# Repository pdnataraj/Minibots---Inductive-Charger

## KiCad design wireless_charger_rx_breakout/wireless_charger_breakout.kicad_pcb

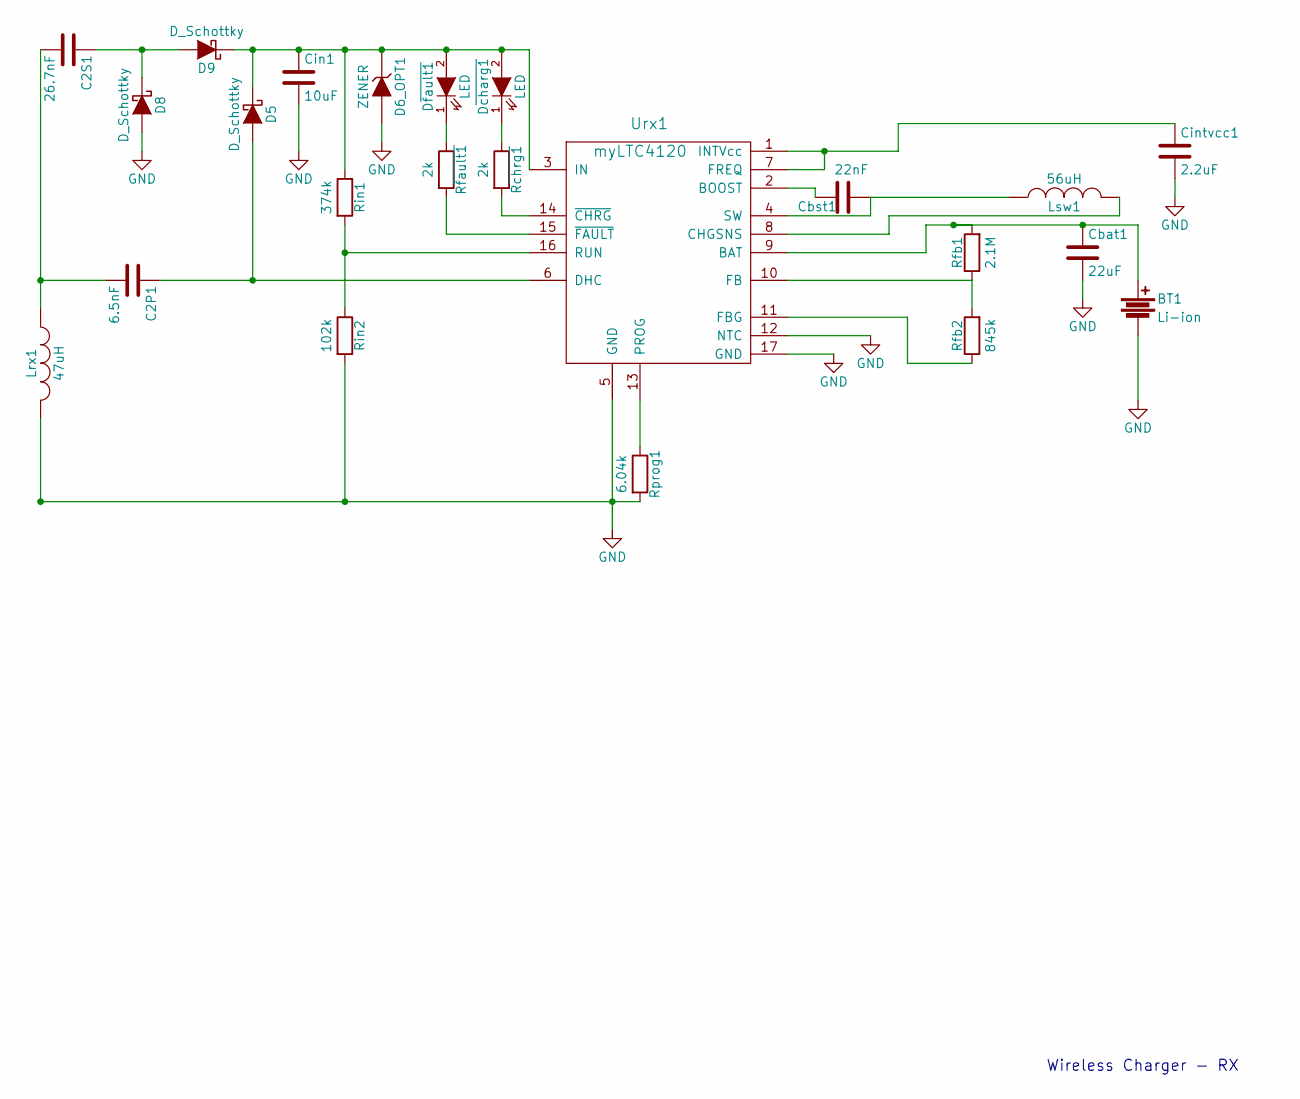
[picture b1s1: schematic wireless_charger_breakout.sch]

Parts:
BT1: Li-ion; Socket_Strip_Straight_1x03
C2P1: 6.5nF; C_1206_HandSoldering
C2S1: 26.7nF; C_1206_HandSoldering
Cbat1: 22uF; C_1206_HandSoldering
Cbst1: 22nF; C_1206_HandSoldering
Cin1: 10uF; C_1206_HandSoldering
Cintvcc1: 2.2uF; C_1206_HandSoldering
D5, D8, D9: D_Schottky; DFLS240L
D6_OPT1: ZENER; SOD-123
D~charg1: LED; LED_1206
D~fault1: LED; LED_1206
Lrx1: 47uH; Receiver_Coil
Lsw1: 56uH; NR6028T470M
Rfb1: 2.1M; R_1206_HandSoldering
Rfb2: 845k; R_1206_HandSoldering
Rin1: 374k; R_1206_HandSoldering
Rin2: 102k; R_1206_HandSoldering
Rprog1: 6.04k; R_1206_HandSoldering
R~chrg1: 2k; R_1206_HandSoldering
R~fault1: 2k; R_1206_HandSoldering
Urx1: myLTC4120; QFN-16-1EP_3x3mm_Pitch0.5mm

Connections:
GND: BT1.2, Cbat1.2, Cin1.2, Cintvcc1.2, D6_OPT1.2 (A), D8.2 (A), Lrx1.2, Rin2.2, Rprog1.2, Urx1.5 (GND), Urx1.12 (NTC), Urx1.17 (GND); also elsewhere on the board
unnamed: BT1.1, Cbat1.1, Rfb1.2, Urx1.9 (BAT)
unnamed: C2P1.1, D5.2 (A), Urx1.6 (DHC)
unnamed 3: C2P1.2, C2S1.2, Lrx1.1; also elsewhere on the board
unnamed: C2S1.1, D8.1 (K), D9.2 (A)
unnamed: Cbst1.1, Lsw1.1, Urx1.4 (SW)
unnamed: Cbst1.2, Urx1.2 (BOOST)
unnamed: Cin1.1, D5.1 (K), D6_OPT1.1 (K), D9.1 (K), D~charg1.2 (A), D~fault1.2 (A), Rin1.1, Urx1.3 (IN)
unnamed: Cintvcc1.1, Urx1.1 (INTVcc), Urx1.7 (FREQ)
unnamed: D~charg1.1 (K), R~chrg1.1
unnamed: D~fault1.1 (K), R~fault1.1
unnamed: Lsw1.2, Urx1.8 (CHGSNS)
unnamed: Rfb1.1, Rfb2.2, Urx1.10 (FB)
unnamed: Rfb2.1, Urx1.11 (FBG)
unnamed: Rin1.2, Rin2.1, Urx1.16 (RUN)
unnamed: Rprog1.1, Urx1.13 (PROG)
unnamed: R~chrg1.2, Urx1.14 (~CHRG)
unnamed: R~fault1.2, Urx1.15 (~FAULT)

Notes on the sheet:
Wireless Charger - RX

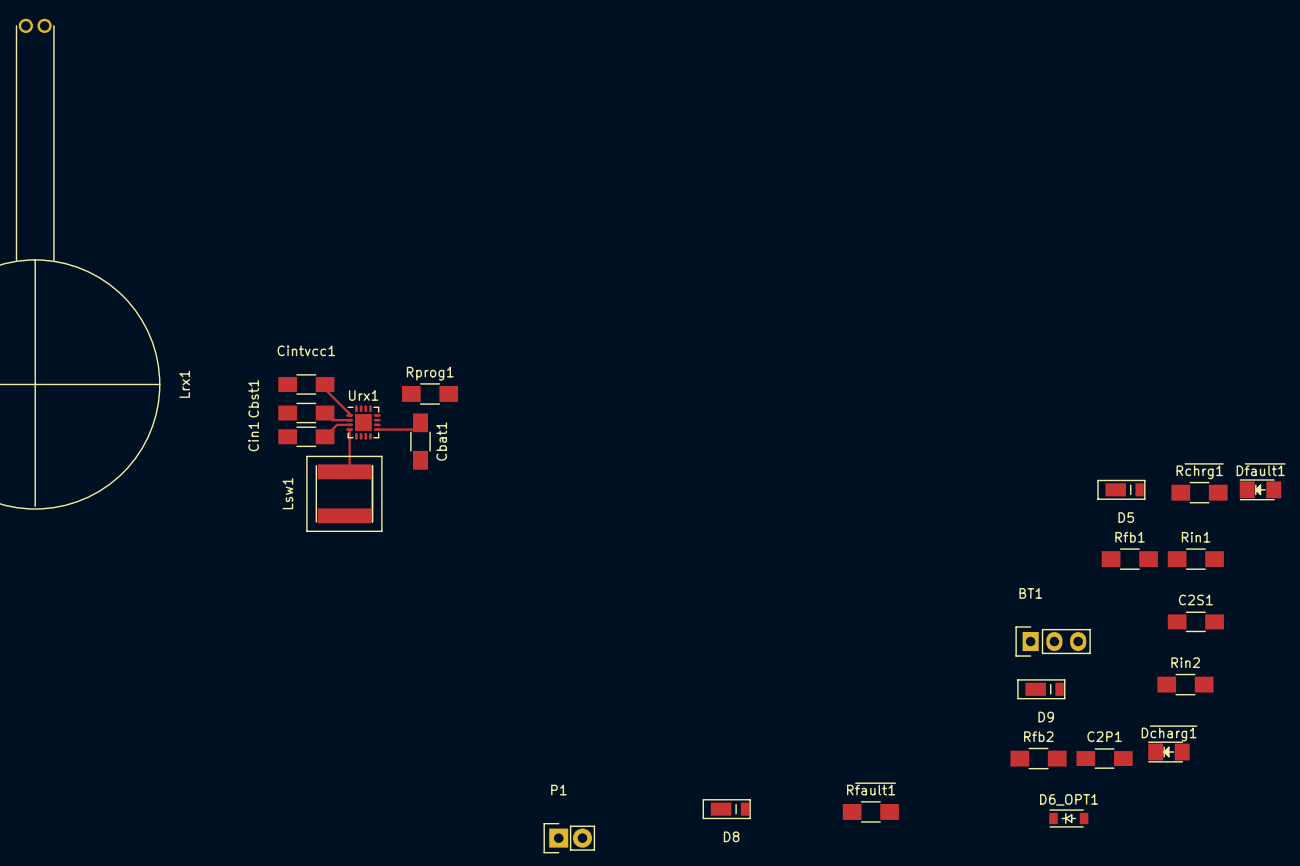
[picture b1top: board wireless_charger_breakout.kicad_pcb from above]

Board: 2 copper layers, 24 parts (0 on the bottom side), 18 nets.

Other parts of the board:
P1: CONN_01X02; Socket_Strip_Straight_1x02

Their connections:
GND: P1.2; also elsewhere on the board
unnamed 3: P1.1; also elsewhere on the board

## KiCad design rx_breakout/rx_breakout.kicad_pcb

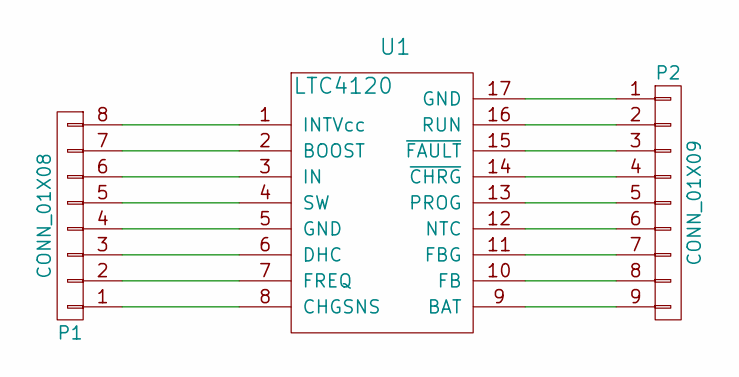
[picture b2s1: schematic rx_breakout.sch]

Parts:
P1: CONN_01X08; Socket_Strip_Straight_1x08
P2: CONN_01X09; Socket_Strip_Straight_1x09
U1: LTC4120; QFN-16-1EP_3x3mm_Pitch0.5mm

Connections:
unnamed: P1.1, U1.8 (CHGSNS)
unnamed: P1.2, U1.7 (FREQ)
unnamed: P1.3, U1.6 (DHC)
unnamed: P1.4, U1.5 (GND)
unnamed: P1.5, U1.4 (SW)
unnamed: P1.6, U1.3 (IN)
unnamed: P1.7, U1.2 (BOOST)
unnamed: P1.8, U1.1 (INTVcc)
unnamed: P2.1, U1.17 (GND)
unnamed: P2.2, U1.16 (RUN)
unnamed: P2.3, U1.15 (~FAULT)
unnamed: P2.4, U1.14 (~CHRG)
unnamed: P2.5, U1.13 (PROG)
unnamed: P2.6, U1.12 (NTC)
unnamed: P2.7, U1.11 (FBG)
unnamed: P2.8, U1.10 (FB)
unnamed: P2.9, U1.9 (BAT)

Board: 2 copper layers, 3 parts (0 on the bottom side), 17 nets, no tracks yet.
